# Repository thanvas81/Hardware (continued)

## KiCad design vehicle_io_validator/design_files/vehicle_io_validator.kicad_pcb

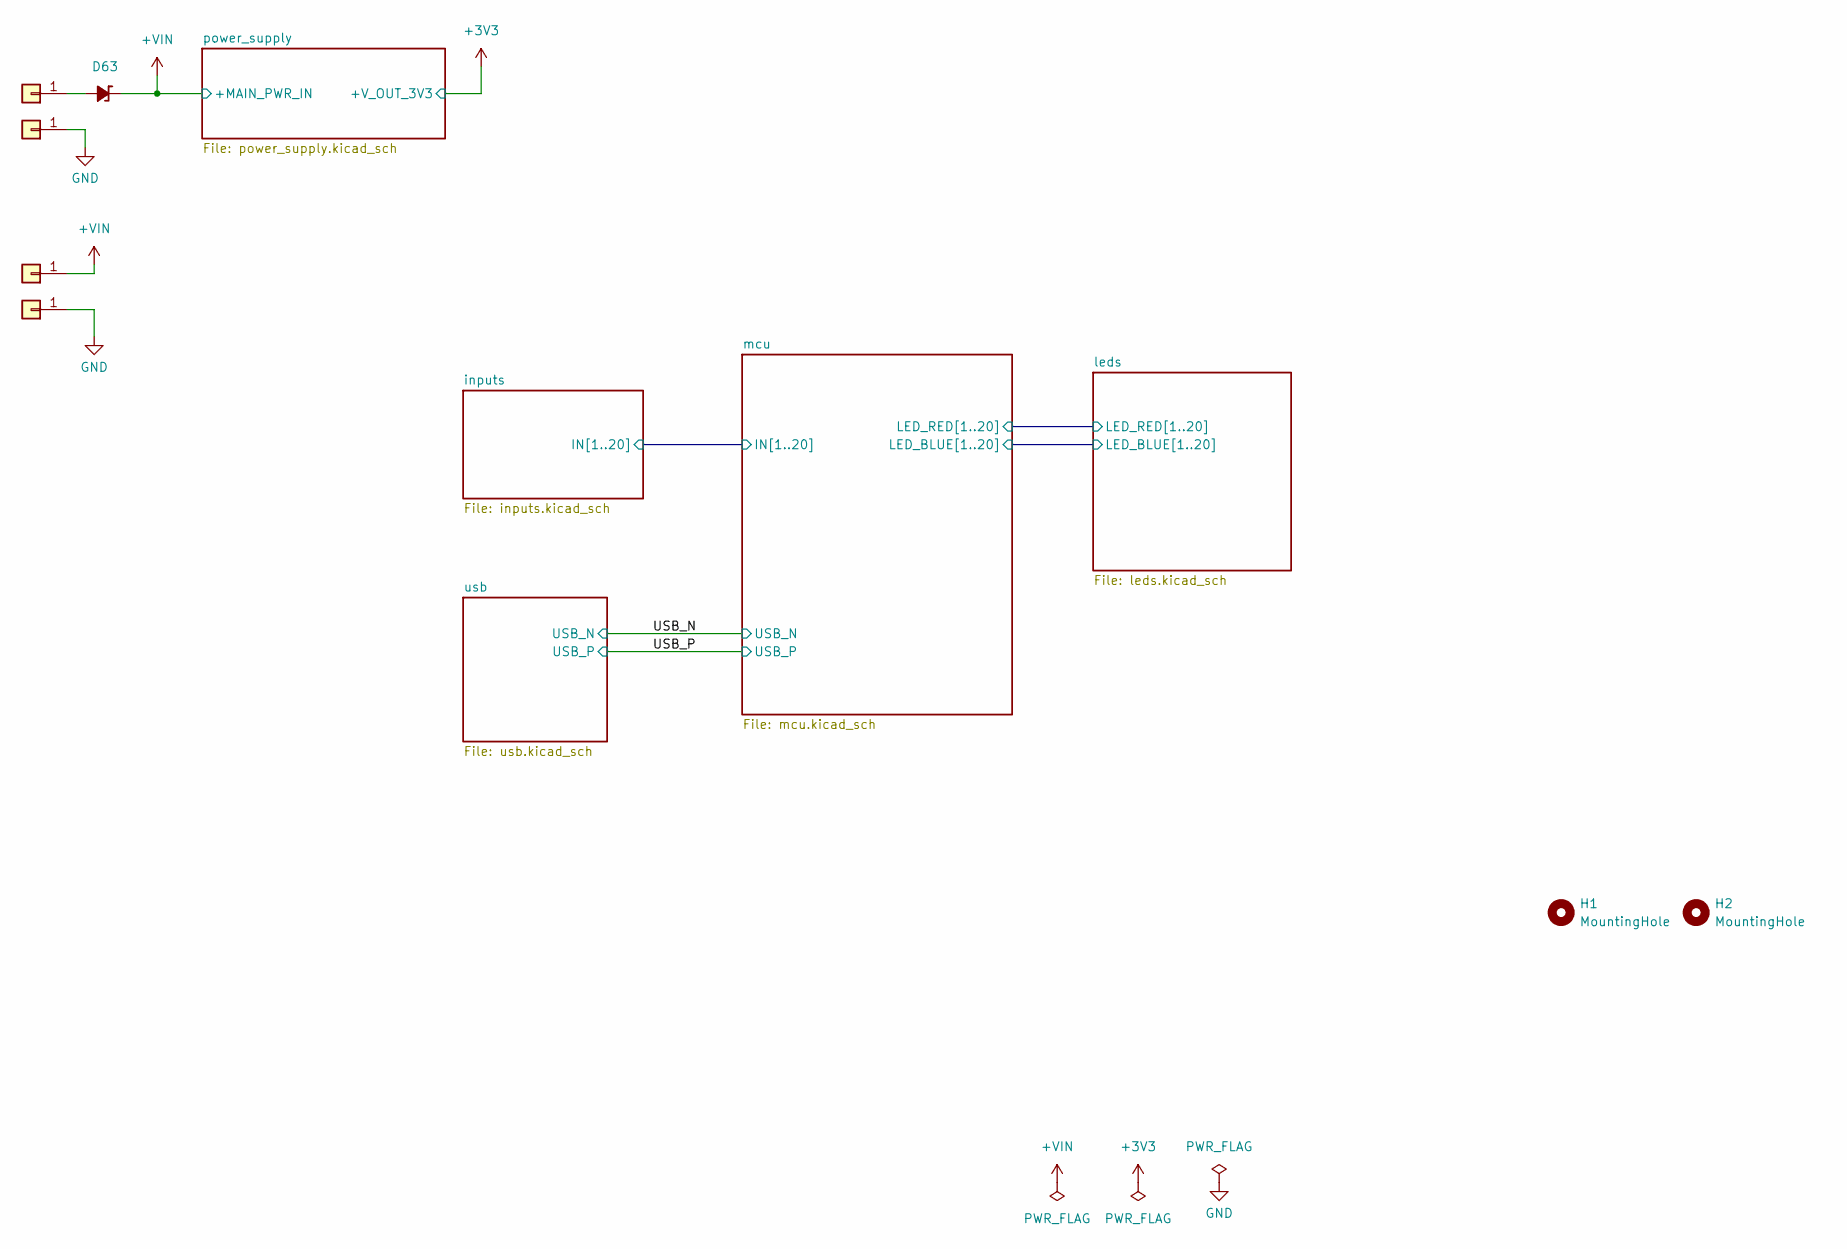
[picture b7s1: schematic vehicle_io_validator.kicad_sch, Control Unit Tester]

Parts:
D63: SMAJ40CAe3/TR13; D_SMA
H1, H2: MountingHole; MountingHole_4.3mm_M4_DIN965
J21, J23, J25, J26: Conn_01x01; Simple_hole_pad_3x1.5

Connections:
+VIN: D63.1 (K), J25.1; also elsewhere on the board
GND: J23.1, J26.1; also elsewhere on the board
unnamed: D63.2 (A), J21.1

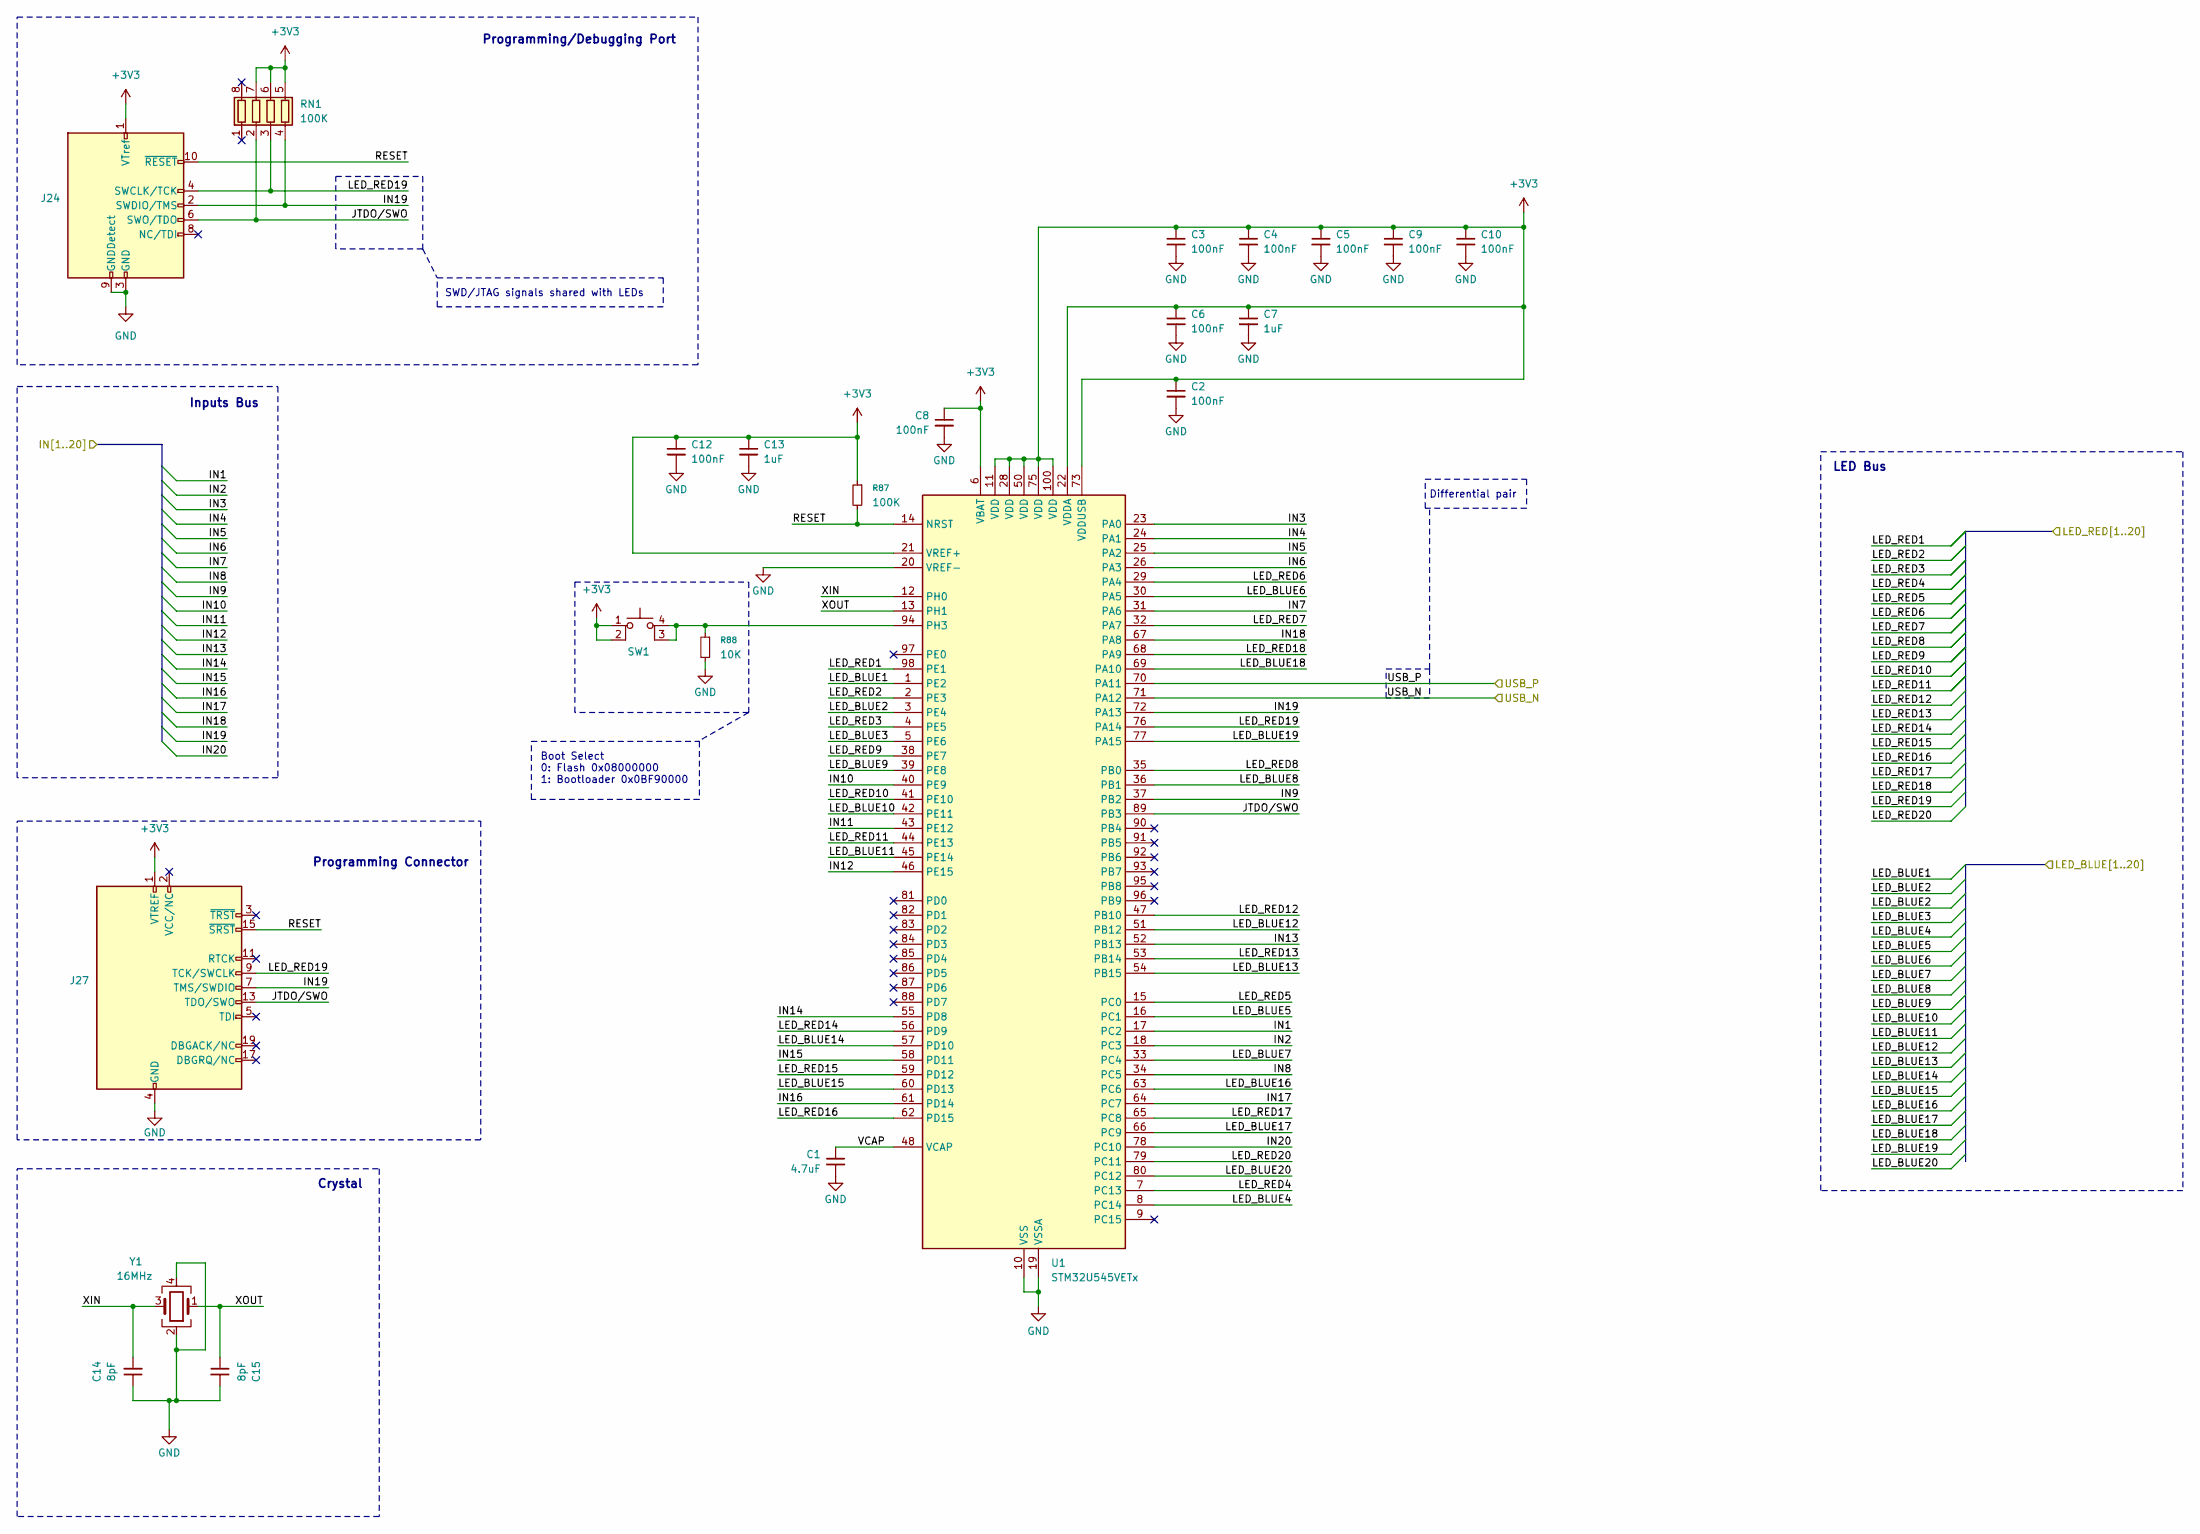
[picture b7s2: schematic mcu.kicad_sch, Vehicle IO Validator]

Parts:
C1: 4.7uF; C_0603_1608Metric
C2, C3, C4, C5, C6, C8, C9, C10, C12: 100nF; C_0603_1608Metric
C7, C13: 1uF; C_0603_1608Metric
C14, C15: 8pF; C_0603_1608Metric
J24: Conn_ARM_JTAG_SWD_10; Tag-Connect_TC2050-IDC-NL_2x05_P1.27mm_Vertical
J27: Conn_ARM_JTAG_SWD_20; PinHeader_2x10_P2.54mm_Vertical
R87: 100K; R_0603_1608Metric
R88: 10K; R_0603_1608Metric
RN1: 100K; R_Array_Concave_4x0603
SW1: KMR221GLFS
U1: STM32U545VETx; LQFP-100_14x14mm_P0.5mm
Y1: 16MHz; Crystal_SMD_Abracon_ABM8AIG-4Pin_3.2x2.5mm; PartID 2167

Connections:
+3V3: C2.1, C3.1, C4.1, C5.1, C6.1, C7.1, C8.1, C9.1, C10.1, C12.1, C13.1, J24.1 (VTref), J27.1 (VTREF), R87.1, RN1.5 (R4.2), RN1.6 (R3.2), RN1.7 (R2.2), SW1.1, SW1.2, U1.6 (VBAT), U1.11 (VDD), U1.21 (VREF+), U1.22 (VDDA), U1.28 (VDD), U1.50 (VDD), U1.73 (VDDUSB), U1.75 (VDD), U1.100 (VDD); also elsewhere on the board
/USB_N: U1.71 (PA12); also elsewhere on the board
/USB_P: U1.70 (PA11); also elsewhere on the board
/inputs/IN1: U1.17 (PC2); also elsewhere on the board
/inputs/IN2: U1.18 (PC3); also elsewhere on the board
/inputs/IN3: U1.23 (PA0); also elsewhere on the board
/inputs/IN4: U1.24 (PA1); also elsewhere on the board
/inputs/IN5: U1.25 (PA2); also elsewhere on the board
/inputs/IN6: U1.26 (PA3); also elsewhere on the board
/inputs/IN7: U1.31 (PA6); also elsewhere on the board
/inputs/IN8: U1.34 (PC5); also elsewhere on the board
/inputs/IN9: U1.37 (PB2); also elsewhere on the board
/inputs/IN10: U1.40 (PE9); also elsewhere on the board
/inputs/IN11: U1.43 (PE12); also elsewhere on the board
/inputs/IN12: U1.46 (PE15); also elsewhere on the board
/inputs/IN13: U1.52 (PB13); also elsewhere on the board
/inputs/IN14: U1.55 (PD8); also elsewhere on the board
/inputs/IN15: U1.58 (PD11); also elsewhere on the board
/inputs/IN16: U1.61 (PD14); also elsewhere on the board
/inputs/IN17: U1.64 (PC7); also elsewhere on the board
/inputs/IN18: U1.67 (PA8); also elsewhere on the board
/inputs/IN19: J24.2 (SWDIO/TMS), J27.7 (TMS/SWDIO), RN1.4 (R4.1), U1.72 (PA13); also elsewhere on the board
/inputs/IN20: U1.78 (PC10); also elsewhere on the board
/leds/LED_BLUE1: U1.1 (PE2); also elsewhere on the board
/leds/LED_BLUE2: U1.3 (PE4); also elsewhere on the board
/leds/LED_BLUE3: U1.5 (PE6); also elsewhere on the board
/leds/LED_BLUE4: U1.8 (PC14); also elsewhere on the board
/leds/LED_BLUE5: U1.16 (PC1); also elsewhere on the board
/leds/LED_BLUE6: U1.30 (PA5); also elsewhere on the board
/leds/LED_BLUE7: U1.33 (PC4); also elsewhere on the board
/leds/LED_BLUE8: U1.36 (PB1); also elsewhere on the board
/leds/LED_BLUE9: U1.39 (PE8); also elsewhere on the board
/leds/LED_BLUE10: U1.42 (PE11); also elsewhere on the board
/leds/LED_BLUE11: U1.45 (PE14); also elsewhere on the board
/leds/LED_BLUE12: U1.51 (PB12); also elsewhere on the board
/leds/LED_BLUE13: U1.54 (PB15); also elsewhere on the board
/leds/LED_BLUE14: U1.57 (PD10); also elsewhere on the board
/leds/LED_BLUE15: U1.60 (PD13); also elsewhere on the board
/leds/LED_BLUE16: U1.63 (PC6); also elsewhere on the board
/leds/LED_BLUE17: U1.66 (PC9); also elsewhere on the board
/leds/LED_BLUE18: U1.69 (PA10); also elsewhere on the board
/leds/LED_BLUE19: U1.77 (PA15); also elsewhere on the board
/leds/LED_BLUE20: U1.80 (PC12); also elsewhere on the board
/leds/LED_RED1: U1.98 (PE1); also elsewhere on the board
/leds/LED_RED2: U1.2 (PE3); also elsewhere on the board
/leds/LED_RED3: U1.4 (PE5); also elsewhere on the board
/leds/LED_RED4: U1.7 (PC13); also elsewhere on the board
/leds/LED_RED5: U1.15 (PC0); also elsewhere on the board
/leds/LED_RED6: U1.29 (PA4); also elsewhere on the board
/leds/LED_RED7: U1.32 (PA7); also elsewhere on the board
/leds/LED_RED8: U1.35 (PB0); also elsewhere on the board
/leds/LED_RED9: U1.38 (PE7); also elsewhere on the board
/leds/LED_RED10: U1.41 (PE10); also elsewhere on the board
/leds/LED_RED11: U1.44 (PE13); also elsewhere on the board
/leds/LED_RED12: U1.47 (PB10); also elsewhere on the board
/leds/LED_RED13: U1.53 (PB14); also elsewhere on the board
/leds/LED_RED14: U1.56 (PD9); also elsewhere on the board
/leds/LED_RED15: U1.59 (PD12); also elsewhere on the board
/leds/LED_RED16: U1.62 (PD15); also elsewhere on the board
/leds/LED_RED17: U1.65 (PC8); also elsewhere on the board
/leds/LED_RED18: U1.68 (PA9); also elsewhere on the board
/leds/LED_RED19: J24.4 (SWCLK/TCK), J27.9 (TCK/SWCLK), RN1.3 (R3.1), U1.76 (PA14); also elsewhere on the board
/leds/LED_RED20: U1.79 (PC11); also elsewhere on the board
/mcu/JTDO/SWO: J24.6 (SWO/TDO), J27.13 (TDO/SWO), RN1.2 (R2.1), U1.89 (PB3)
/mcu/RESET: J24.10 (~RESET), J27.15 (~SRST), R87.2, U1.14 (NRST)
/mcu/VCAP: C1.1, U1.48 (VCAP)
/mcu/XIN: C14.2, U1.12 (PH0), Y1.3
/mcu/XOUT: C15.1, U1.13 (PH1), Y1.1
GND: C1.2, C2.2, C3.2, C4.2, C5.2, C6.2, C7.2, C8.2, C9.2, C10.2, C12.2, C13.2, C14.1, C15.2, J24.3 (GND), J24.5 (GND), J24.9 (GNDDetect), J27.4 (GND), J27.6 (GND), J27.8 (GND), J27.10 (GND), J27.12 (GND), J27.14 (GND), J27.16 (GND), J27.18 (GND), J27.20 (GND), R88.2, U1.10 (VSS), U1.19 (VSSA), U1.20 (VREF-), U1.27 (VSS), U1.49 (VSS), U1.74 (VSS), U1.99 (VSS), Y1.2, Y1.4; also elsewhere on the board
unnamed: R88.1, SW1.3 (K), SW1.4 (A), U1.94 (PH3)

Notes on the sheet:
Differential pair
SWD/JTAG signals shared with LEDs
Inputs Bus
Crystal
LED Bus
Programming/Debugging Port
Programming Connector
Boot Select 0: Flash 0x08000000 1: Bootloader 0x0BF90000

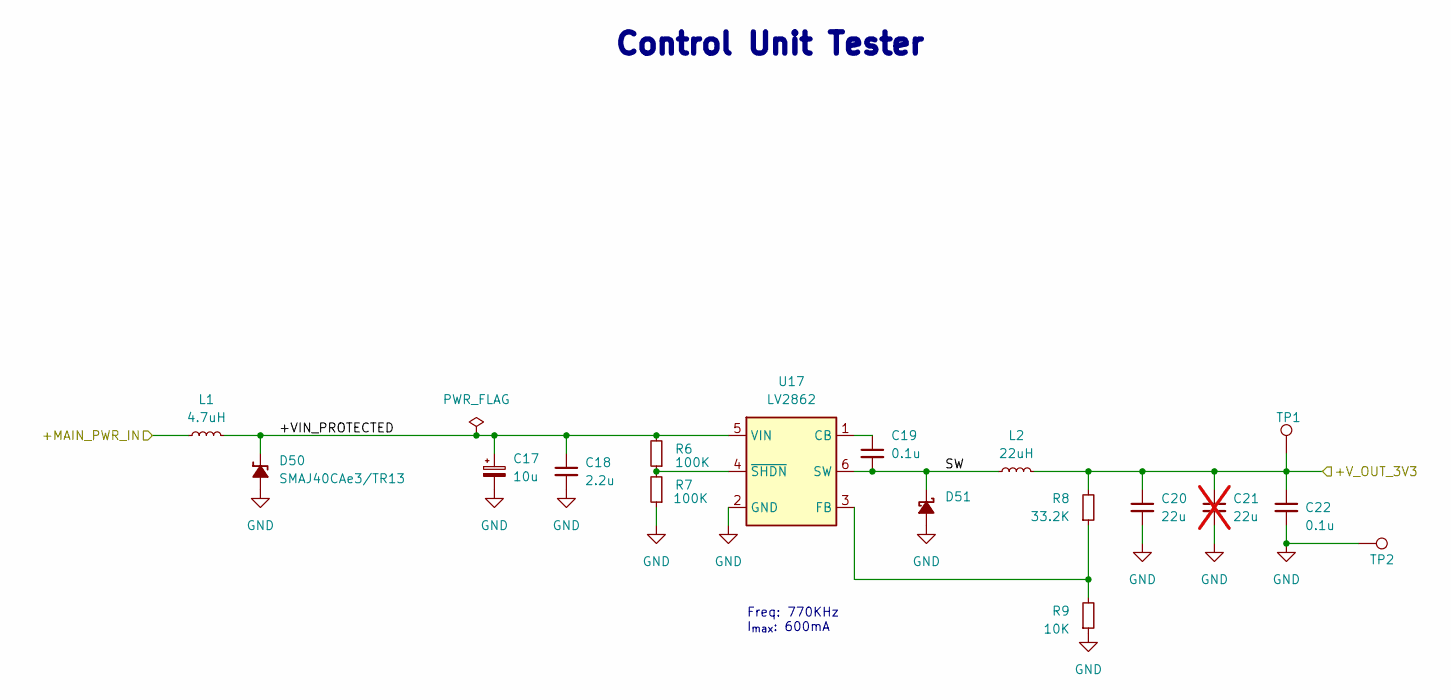
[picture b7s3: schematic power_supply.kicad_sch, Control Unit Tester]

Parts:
C17: 10u; CP_Elec_5x5.3
C18: 2.2u; C_1210_3225Metric
C19, C22: 0.1u; C_0603_1608Metric; PartkeeprID 50
C20: 22u; C_1210_3225Metric; PartkeeprID 45
C21: 22u; C_1210_3225Metric; PartkeeprID 45; not fitted
D50: SMAJ40CAe3/TR13; D_SMA
D51: SBR3U60P1Q-7; D_PowerDI-123
L1: 4.7uH; L_TDK_VLS252012HBX; PartkeeprID 44
L2: 22uH; L_Taiyo-Yuden_NR-50xx; PartkeeprID 44
R6, R7: 100K; R_0603_1608Metric; PartkeeprID 47
R8: 33.2K; R_0603_1608Metric; PartkeeprID 49
R9: 10K; R_0603_1608Metric; PartkeeprID 48
TP1, TP2: TestPoint; TestPoint_Pad_D1.5mm
U17: LV2862; SOT-23-6; PartkeeprID 46

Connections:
+3V3: C20.1, C21.1, C22.1, L2.2, R8.2, TP1.1; also elsewhere on the board
+VIN: L1.1; also elsewhere on the board
/power_supply/+VIN_PROTECTED: C17.1, C18.1, D50.1 (K), L1.2, R6.2, U17.5 (VIN)
/power_supply/SW: C19.2, D51.1 (K), L2.1, U17.6 (SW)
GND: C17.2, C18.2, C20.2, C21.2, C22.2, D50.2 (A), D51.2 (A), R7.1, R9.1, TP2.1, U17.2 (GND); also elsewhere on the board
unnamed: C19.1, U17.1 (CB)
unnamed: R8.1, R9.2, U17.3 (FB)
unnamed: R6.1, R7.2, U17.4 (~SHDN)

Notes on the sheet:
${TITLE}
Freq: 770KHz I_{max}: 600mA

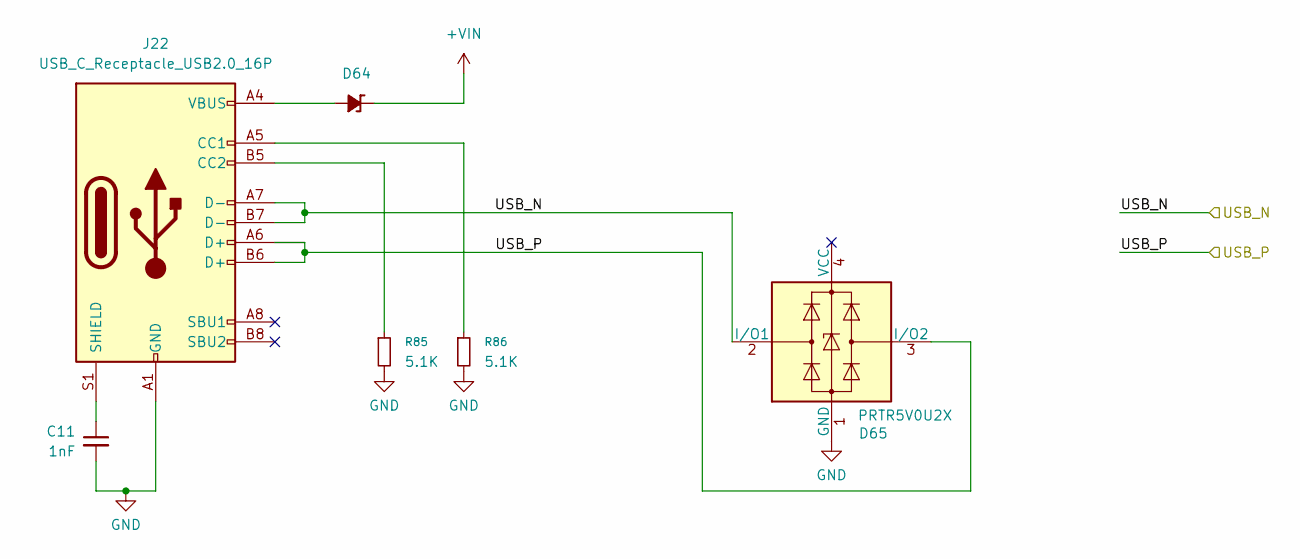
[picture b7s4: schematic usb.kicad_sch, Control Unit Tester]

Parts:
C11: 1nF; C_1206_3216Metric
D64: SMAJ40CAe3/TR13; D_SMA
D65: PRTR5V0U2X; SOT-143; PartID 2166
J22: USB_C_Receptacle_USB2.0_16P; USB_C_Receptacle_GCT_USB4105-xx-A_16P_TopMnt_Horizontal; PartID 2165
R85, R86: 5.1K; R_0603_1608Metric

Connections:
+VIN: D64.1 (K); also elsewhere on the board
/USB_N: D65.2 (I/O1), J22.A7 (D-), J22.B7 (D-); also elsewhere on the board
/USB_P: D65.3 (I/O2), J22.A6 (D+), J22.B6 (D+); also elsewhere on the board
GND: C11.2, D65.1 (GND), J22.A1 (GND), J22.A12 (GND), J22.B1 (GND), J22.B12 (GND), R85.2, R86.2; also elsewhere on the board
unnamed: D64.2 (A), J22.A4 (VBUS), J22.A9 (VBUS), J22.B4 (VBUS), J22.B9 (VBUS)
unnamed: J22.A5 (CC1), R86.1
unnamed: J22.B5 (CC2), R85.1
unnamed: C11.1, J22.S1 (SHIELD)

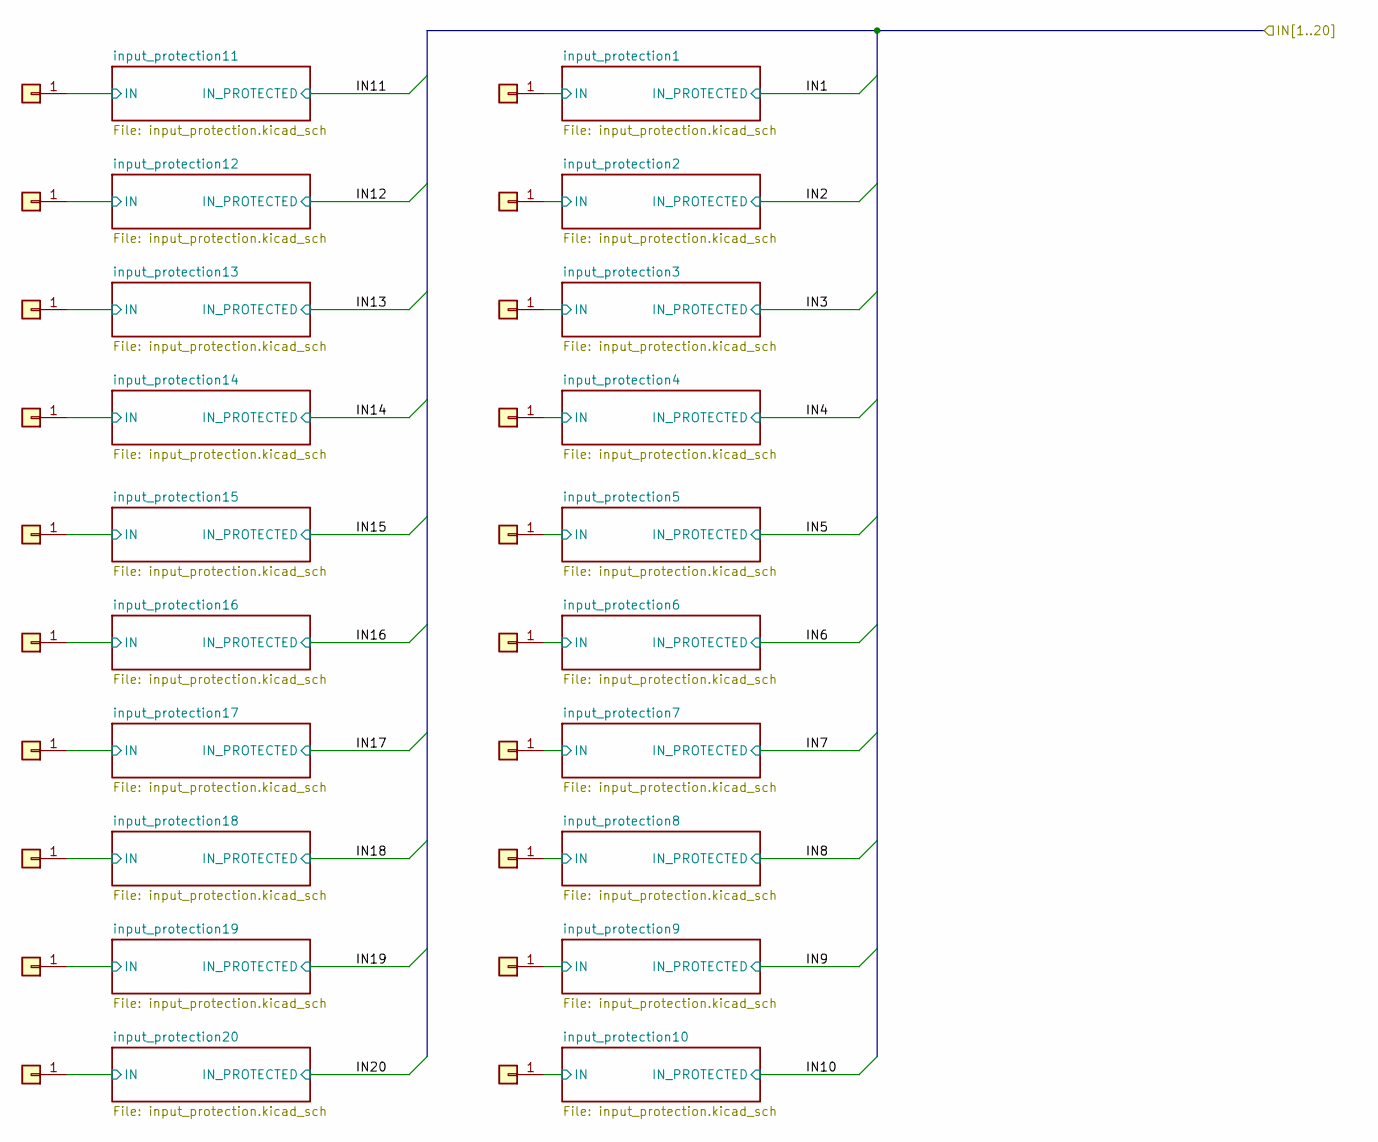
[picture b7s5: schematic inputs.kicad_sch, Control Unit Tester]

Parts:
J1, J2, J3, J4, J5, J6, J7, J8, J9, J10, J11, J12, J13, J14, J15, J16, J17, J18, J19, J20: Conn_01x01; Simple_hole_pad_3x1.5

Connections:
/inputs/input_protection1/IN: J20.1; also elsewhere on the board
/inputs/input_protection2/IN: J19.1; also elsewhere on the board
/inputs/input_protection3/IN: J18.1; also elsewhere on the board
/inputs/input_protection4/IN: J17.1; also elsewhere on the board
/inputs/input_protection5/IN: J16.1; also elsewhere on the board
/inputs/input_protection6/IN: J15.1; also elsewhere on the board
/inputs/input_protection7/IN: J14.1; also elsewhere on the board
/inputs/input_protection8/IN: J13.1; also elsewhere on the board
/inputs/input_protection9/IN: J12.1; also elsewhere on the board
/inputs/input_protection10/IN: J11.1; also elsewhere on the board
/inputs/input_protection11/IN: J1.1; also elsewhere on the board
/inputs/input_protection12/IN: J2.1; also elsewhere on the board
/inputs/input_protection13/IN: J3.1; also elsewhere on the board
/inputs/input_protection14/IN: J4.1; also elsewhere on the board
/inputs/input_protection15/IN: J5.1; also elsewhere on the board
/inputs/input_protection16/IN: J6.1; also elsewhere on the board
/inputs/input_protection17/IN: J7.1; also elsewhere on the board
/inputs/input_protection18/IN: J8.1; also elsewhere on the board
/inputs/input_protection19/IN: J9.1; also elsewhere on the board
/inputs/input_protection20/IN: J10.1; also elsewhere on the board

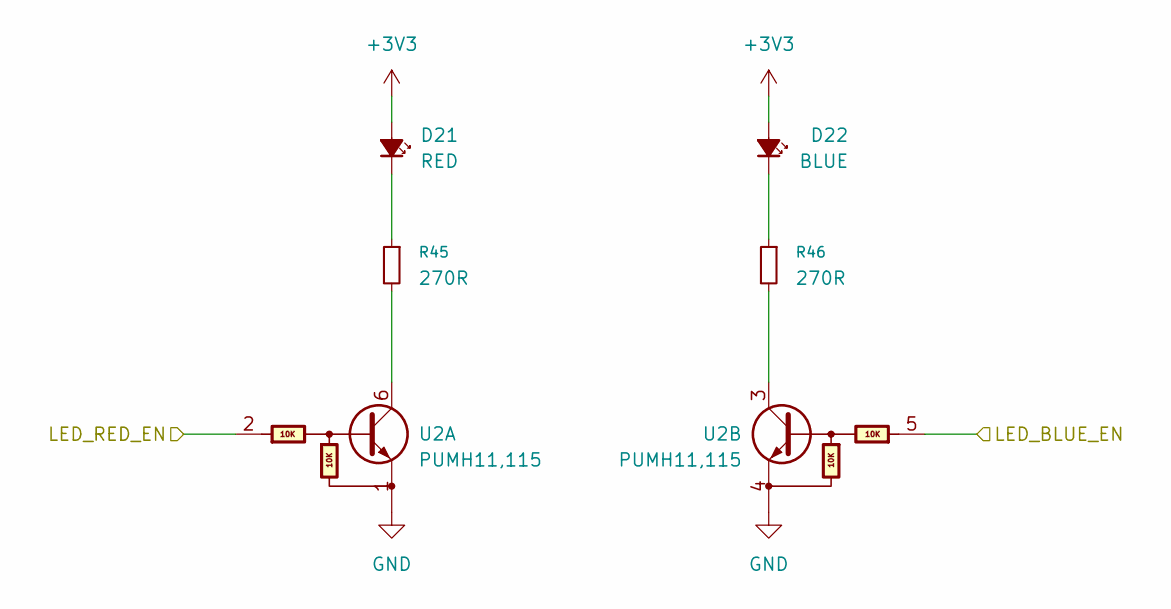
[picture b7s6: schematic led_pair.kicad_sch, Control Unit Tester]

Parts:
D21: RED; LED_0805_2012Metric; PartID 2162
D22: BLUE; LED_0805_2012Metric; PartID 2163
R45, R46: 270R; R_0603_1608Metric
U2: PUMH11,115; SOT-363_SC-70-6; PartID 450

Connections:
+3V3: D21.2 (A), D22.2 (A); also elsewhere on the board
/leds/LED_BLUE1: U2.5; also elsewhere on the board
/leds/LED_RED1: U2.2; also elsewhere on the board
GND: U2.1, U2.4; also elsewhere on the board
unnamed: D21.1 (K), R45.1
unnamed: D22.1 (K), R46.1
unnamed: R45.2, U2.6
unnamed: R46.2, U2.3

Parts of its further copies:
D23, D25, D27, D29, D31, D33, D35, D37, D39, D41, D43, D45, D47, D49, D53, D55, D57, D59, D61: RED; LED_0805_2012Metric; PartID 2162
D24, D26, D28, D30, D32, D34, D36, D38, D40, D42, D44, D46, D48, D52, D54, D56, D58, D60, D62: BLUE; LED_0805_2012Metric; PartID 2163
R47, R48, R49, R50, R51, R52, R53, R54, R55, R56, R57, R58, R59, R60, R61, R62, R63, R64, R65, R66, R67, R68, R69, R70, R71, R72, R73, R74, R75, R76, R77, R78, R79, R80, R81, R82, R83, R84: 270R; R_0603_1608Metric
U3, U4, U5, U6, U7, U8, U9, U10, U11, U12, U13, U14, U15, U16, U18, U19, U20, U21, U22: PUMH11,115; SOT-363_SC-70-6; PartID 450

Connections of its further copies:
+3V3: D23.2 (A), D24.2 (A), D25.2 (A), D26.2 (A), D27.2 (A), D28.2 (A), D29.2 (A), D30.2 (A), D31.2 (A), D32.2 (A), D33.2 (A), D34.2 (A), D35.2 (A), D36.2 (A), D37.2 (A), D38.2 (A), D39.2 (A), D40.2 (A), D41.2 (A), D42.2 (A), D43.2 (A), D44.2 (A), D45.2 (A), D46.2 (A), D47.2 (A), D48.2 (A), D49.2 (A), D52.2 (A), D53.2 (A), D54.2 (A), D55.2 (A), D56.2 (A), D57.2 (A), D58.2 (A), D59.2 (A), D60.2 (A), D61.2 (A), D62.2 (A); also elsewhere on the board
/leds/LED_BLUE2: U3.5; also elsewhere on the board
/leds/LED_BLUE3: U4.5; also elsewhere on the board
/leds/LED_BLUE4: U5.5; also elsewhere on the board
/leds/LED_BLUE5: U6.5; also elsewhere on the board
/leds/LED_BLUE6: U7.5; also elsewhere on the board
/leds/LED_BLUE7: U8.5; also elsewhere on the board
/leds/LED_BLUE8: U9.5; also elsewhere on the board
/leds/LED_BLUE9: U10.5; also elsewhere on the board
/leds/LED_BLUE10: U11.5; also elsewhere on the board
/leds/LED_BLUE11: U12.5; also elsewhere on the board
/leds/LED_BLUE12: U13.5; also elsewhere on the board
/leds/LED_BLUE13: U14.5; also elsewhere on the board
/leds/LED_BLUE14: U15.5; also elsewhere on the board
/leds/LED_BLUE15: U16.5; also elsewhere on the board
/leds/LED_BLUE16: U18.5; also elsewhere on the board
/leds/LED_BLUE17: U19.5; also elsewhere on the board
/leds/LED_BLUE18: U20.5; also elsewhere on the board
/leds/LED_BLUE19: U21.5; also elsewhere on the board
/leds/LED_BLUE20: U22.5; also elsewhere on the board
/leds/LED_RED2: U3.2; also elsewhere on the board
/leds/LED_RED3: U4.2; also elsewhere on the board
/leds/LED_RED4: U5.2; also elsewhere on the board
/leds/LED_RED5: U6.2; also elsewhere on the board
/leds/LED_RED6: U7.2; also elsewhere on the board
/leds/LED_RED7: U8.2; also elsewhere on the board
/leds/LED_RED8: U9.2; also elsewhere on the board
/leds/LED_RED9: U10.2; also elsewhere on the board
/leds/LED_RED10: U11.2; also elsewhere on the board
/leds/LED_RED11: U12.2; also elsewhere on the board
/leds/LED_RED12: U13.2; also elsewhere on the board
/leds/LED_RED13: U14.2; also elsewhere on the board
/leds/LED_RED14: U15.2; also elsewhere on the board
/leds/LED_RED15: U16.2; also elsewhere on the board
/leds/LED_RED16: U18.2; also elsewhere on the board
/leds/LED_RED17: U19.2; also elsewhere on the board
/leds/LED_RED18: U20.2; also elsewhere on the board
/leds/LED_RED19: U21.2; also elsewhere on the board
/leds/LED_RED20: U22.2; also elsewhere on the board
GND: U3.1, U3.4, U4.1, U4.4, U5.1, U5.4, U6.1, U6.4, U7.1, U7.4, U8.1, U8.4, U9.1, U9.4, U10.1, U10.4, U11.1, U11.4, U12.1, U12.4, U13.1, U13.4, U14.1, U14.4, U15.1, U15.4, U16.1, U16.4, U18.1, U18.4, U19.1, U19.4, U20.1, U20.4, U21.1, U21.4, U22.1, U22.4; also elsewhere on the board
unnamed: D23.1 (K), R47.1
unnamed: D24.1 (K), R48.1
unnamed: D25.1 (K), R49.1
unnamed: D26.1 (K), R50.1
unnamed: D27.1 (K), R51.1
unnamed: D28.1 (K), R52.1
unnamed: D29.1 (K), R53.1
unnamed: D30.1 (K), R54.1
unnamed: D31.1 (K), R55.1
unnamed: D32.1 (K), R56.1
unnamed: D33.1 (K), R57.1
unnamed: D34.1 (K), R58.1
unnamed: D35.1 (K), R59.1
unnamed: D36.1 (K), R60.1
unnamed: D37.1 (K), R61.1
unnamed: D38.1 (K), R62.1
unnamed: D39.1 (K), R63.1
unnamed: D40.1 (K), R64.1
unnamed: D41.1 (K), R65.1
unnamed: D42.1 (K), R66.1
unnamed: D43.1 (K), R67.1
unnamed: D44.1 (K), R68.1
unnamed: D45.1 (K), R69.1
unnamed: D46.1 (K), R70.1
unnamed: D47.1 (K), R71.1
unnamed: D48.1 (K), R72.1
unnamed: D49.1 (K), R73.1
unnamed: D52.1 (K), R74.1
unnamed: D53.1 (K), R75.1
unnamed: D54.1 (K), R76.1
unnamed: D55.1 (K), R77.1
unnamed: D56.1 (K), R78.1
unnamed: D57.1 (K), R79.1
unnamed: D58.1 (K), R80.1
unnamed: D59.1 (K), R81.1
unnamed: D60.1 (K), R82.1
unnamed: D61.1 (K), R83.1
unnamed: D62.1 (K), R84.1
unnamed: R47.2, U3.6
unnamed: R48.2, U3.3
unnamed: R49.2, U4.6
unnamed: R50.2, U4.3
unnamed: R51.2, U5.6
unnamed: R52.2, U5.3
unnamed: R53.2, U6.6
unnamed: R54.2, U6.3
unnamed: R55.2, U7.6
unnamed: R56.2, U7.3
unnamed: R57.2, U8.6
unnamed: R58.2, U8.3
unnamed: R59.2, U9.6
unnamed: R60.2, U9.3
unnamed: R61.2, U10.6
unnamed: R62.2, U10.3
unnamed: R63.2, U11.6
unnamed: R64.2, U11.3
unnamed: R65.2, U12.6
unnamed: R66.2, U12.3
unnamed: R67.2, U13.6
unnamed: R68.2, U13.3
unnamed: R69.2, U14.6
unnamed: R70.2, U14.3
unnamed: R71.2, U15.6
unnamed: R72.2, U15.3
unnamed: R73.2, U16.6
unnamed: R74.2, U16.3
unnamed: R75.2, U18.6
unnamed: R76.2, U18.3
unnamed: R77.2, U19.6
unnamed: R78.2, U19.3
unnamed: R79.2, U20.6
unnamed: R80.2, U20.3
unnamed: R81.2, U21.6
unnamed: R82.2, U21.3
unnamed: R83.2, U22.6
unnamed: R84.2, U22.3

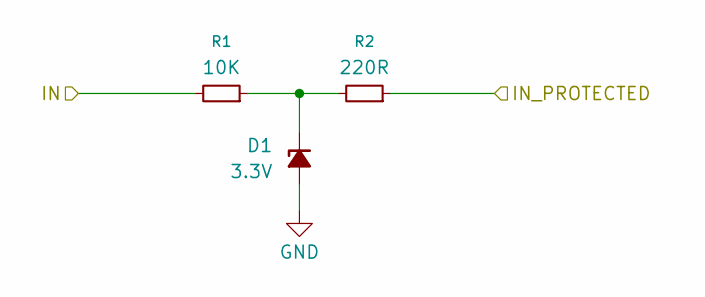
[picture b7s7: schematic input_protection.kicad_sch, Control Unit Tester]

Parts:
D1: 3.3V; D_SOD-323; PartID 2161
R1: 10K; R_0603_1608Metric
R2: 220R; R_0603_1608Metric

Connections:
/inputs/IN20: R2.1; also elsewhere on the board
/inputs/input_protection20/IN: R1.2; also elsewhere on the board
GND: D1.2 (A); also elsewhere on the board
unnamed: D1.1 (K), R1.1, R2.2

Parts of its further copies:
D2, D3, D4, D5, D6, D7, D8, D9, D10, D11, D12, D13, D14, D15, D16, D17, D18, D19, D20: 3.3V; D_SOD-323; PartID 2161
R3, R5, R11, R13, R15, R17, R19, R21, R23, R25, R27, R29, R31, R33, R35, R37, R39, R41, R43: 10K; R_0603_1608Metric
R4, R10, R12, R14, R16, R18, R20, R22, R24, R26, R28, R30, R32, R34, R36, R38, R40, R42, R44: 220R; R_0603_1608Metric

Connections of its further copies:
/inputs/IN1: R4.1; also elsewhere on the board
/inputs/IN2: R10.1; also elsewhere on the board
/inputs/IN3: R12.1; also elsewhere on the board
/inputs/IN4: R14.1; also elsewhere on the board
/inputs/IN5: R16.1; also elsewhere on the board
/inputs/IN6: R18.1; also elsewhere on the board
/inputs/IN7: R20.1; also elsewhere on the board
/inputs/IN8: R22.1; also elsewhere on the board
/inputs/IN9: R24.1; also elsewhere on the board
/inputs/IN10: R26.1; also elsewhere on the board
/inputs/IN11: R28.1; also elsewhere on the board
/inputs/IN12: R30.1; also elsewhere on the board
/inputs/IN13: R32.1; also elsewhere on the board
/inputs/IN14: R34.1; also elsewhere on the board
/inputs/IN15: R36.1; also elsewhere on the board
/inputs/IN16: R38.1; also elsewhere on the board
/inputs/IN17: R40.1; also elsewhere on the board
/inputs/IN18: R42.1; also elsewhere on the board
/inputs/IN19: R44.1; also elsewhere on the board
/inputs/input_protection1/IN: R3.2; also elsewhere on the board
/inputs/input_protection2/IN: R5.2; also elsewhere on the board
/inputs/input_protection3/IN: R11.2; also elsewhere on the board
/inputs/input_protection4/IN: R13.2; also elsewhere on the board
/inputs/input_protection5/IN: R15.2; also elsewhere on the board
/inputs/input_protection6/IN: R17.2; also elsewhere on the board
/inputs/input_protection7/IN: R19.2; also elsewhere on the board
/inputs/input_protection8/IN: R21.2; also elsewhere on the board
/inputs/input_protection9/IN: R23.2; also elsewhere on the board
/inputs/input_protection10/IN: R25.2; also elsewhere on the board
/inputs/input_protection11/IN: R27.2; also elsewhere on the board
/inputs/input_protection12/IN: R29.2; also elsewhere on the board
/inputs/input_protection13/IN: R31.2; also elsewhere on the board
/inputs/input_protection14/IN: R33.2; also elsewhere on the board
/inputs/input_protection15/IN: R35.2; also elsewhere on the board
/inputs/input_protection16/IN: R37.2; also elsewhere on the board
/inputs/input_protection17/IN: R39.2; also elsewhere on the board
/inputs/input_protection18/IN: R41.2; also elsewhere on the board
/inputs/input_protection19/IN: R43.2; also elsewhere on the board
GND: D2.2 (A), D3.2 (A), D4.2 (A), D5.2 (A), D6.2 (A), D7.2 (A), D8.2 (A), D9.2 (A), D10.2 (A), D11.2 (A), D12.2 (A), D13.2 (A), D14.2 (A), D15.2 (A), D16.2 (A), D17.2 (A), D18.2 (A), D19.2 (A), D20.2 (A); also elsewhere on the board
unnamed: D2.1 (K), R3.1, R4.2
unnamed: D3.1 (K), R5.1, R10.2
unnamed: D4.1 (K), R11.1, R12.2
unnamed: D5.1 (K), R13.1, R14.2
unnamed: D6.1 (K), R15.1, R16.2
unnamed: D7.1 (K), R17.1, R18.2
unnamed: D8.1 (K), R19.1, R20.2
unnamed: D9.1 (K), R21.1, R22.2
unnamed: D10.1 (K), R23.1, R24.2
unnamed: D11.1 (K), R25.1, R26.2
unnamed: D12.1 (K), R27.1, R28.2
unnamed: D13.1 (K), R29.1, R30.2
unnamed: D14.1 (K), R31.1, R32.2
unnamed: D15.1 (K), R33.1, R34.2
unnamed: D16.1 (K), R35.1, R36.2
unnamed: D17.1 (K), R37.1, R38.2
unnamed: D18.1 (K), R39.1, R40.2
unnamed: D19.1 (K), R41.1, R42.2
unnamed: D20.1 (K), R43.1, R44.2
